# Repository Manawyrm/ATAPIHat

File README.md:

ATAPIHat
=============================

#### Overview

Replaced by https://github.com/Manawyrm/ATAPIHat-SMI  
Directly connected to the GPIOs, much higher speeds.   

**Don't manufacture this board (in either Rev.A or Rev.B).**  
This design isn't optimal at all. 

#### Rev. A Errata
Reset is wrong, is hardpulled to ground. Solution: connect to GPIO17.   
Chip select is non-ideal (solder jumper?)  
Selectable 5V/3.3V on Pin 20 required  
IDE Reset line should be connected to LED7 aka pin 28 of U4  
Signal integrity issues, paralell termination resistors (maybe 120 Ohms) and series termination would be ideal.  

#### Additional info

[Kernel driver](https://github.com/Manawyrm/pata-gpio)  
[Schematic](https://github.com/Manawyrm/ATAPIHat/blob/master/ATAPIHat.pdf)

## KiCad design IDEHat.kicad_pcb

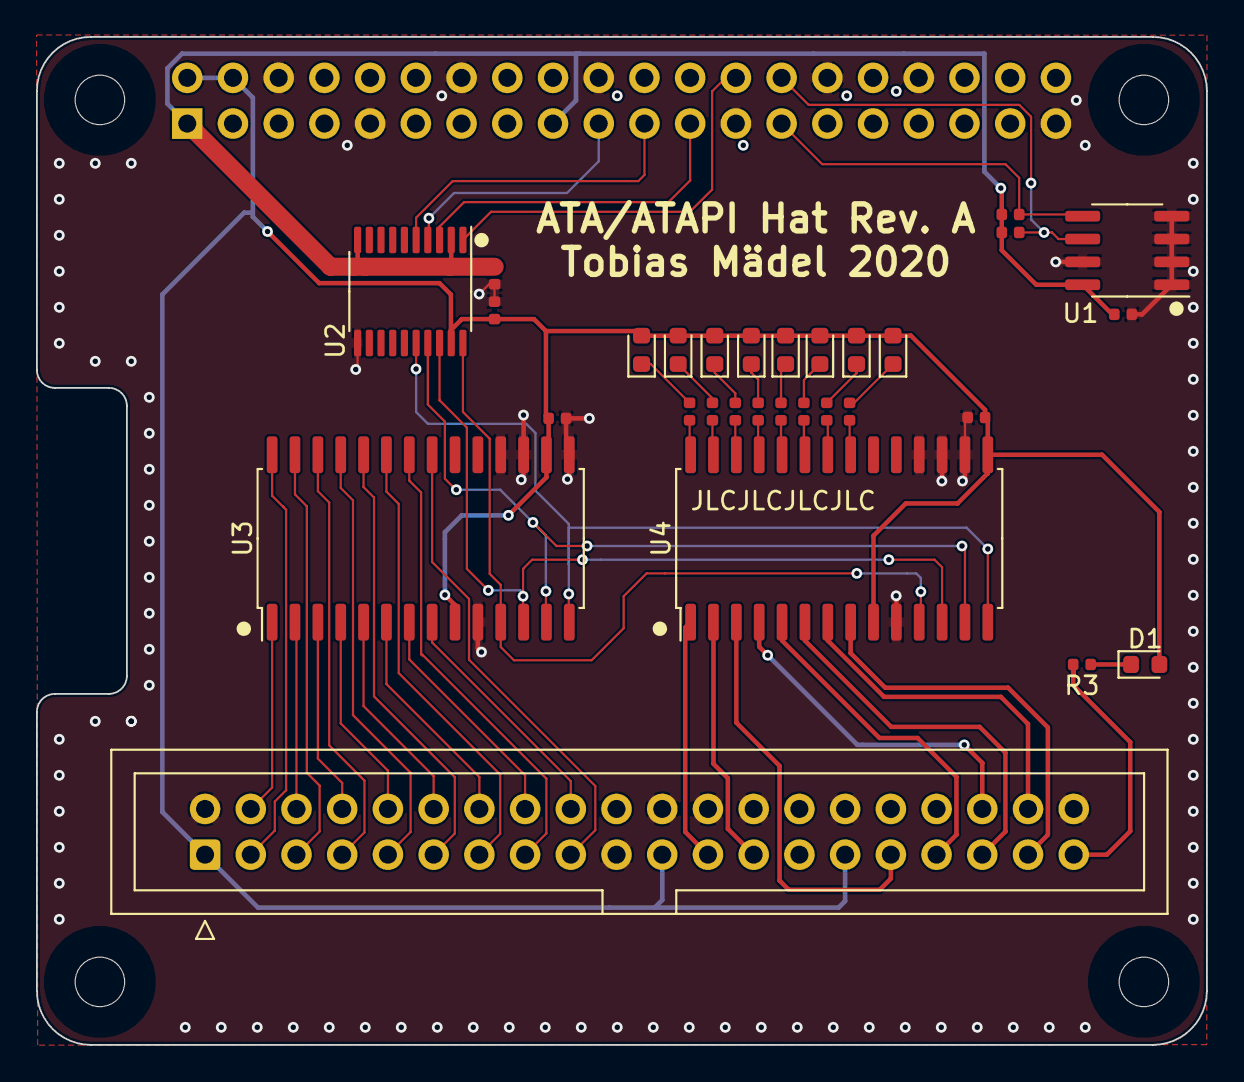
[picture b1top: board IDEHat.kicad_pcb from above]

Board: 2 copper layers, 65.0 x 56.0 mm, 31 parts (1 on the bottom side), 55 nets.

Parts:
C1, C2, C3, C4, C5: 100n; C_0402_1005Metric
D1: LED; LED_0603_1608Metric
D2, D3: Red; LED_0603_1608Metric
D4, D5: Yellow; LED_0603_1608Metric
D6, D7: Green; LED_0603_1608Metric
D8, D9: Blue; LED_0603_1608Metric
J1: Pi; PinSocket_2x20_P2.54mm_Vertical
J2: IDE; IDC-Header_2x20_P2.54mm_Vertical
R1, R2, R3, R4, R5, R6, R7, R10, R11: 4.7k; R_0402_1005Metric
R8, R9: 10k; R_0402_1005Metric
U1: AT24CS32; SOIC-8_3.9x4.9mm_P1.27mm
U2: TXS0108EPW; TSSOP-20_4.4x6.5mm_P0.65mm
U3, U4: MCP23S17_SO; SOIC-28W_7.5x17.9mm_P1.27mm

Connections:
+3V3: C4.1, C5.1, J1.1, J1.17, R1.1, R2.1, U1.8, U2.2, U2.10
+5V: C1.1, C2.1, C3.1, D1.2, D2.2, D3.2, D4.2, D5.2, D6.2, D7.2, D8.2, D9.2, J1.2, J1.4, J2.1, J2.21, J2.29, U2.19, U3.9, U3.16, U4.9, U4.15
/3V_CS: J1.26, U2.1
/3V_MISO: J1.21, U2.5
/3V_MOSI: J1.19, U2.4
/3V_SCK: J1.23, U2.3
/ACTIVE: J2.39, R3.2
/CS: U2.20, U3.11, U4.11
/CS0: J2.37, U4.8
/CS1: J2.38, U4.7
/D0: J2.17, U3.21
/D1: J2.15, U3.22
/D2: J2.13, U3.23
/D3: J2.11, U3.24
/D4: J2.9, U3.25
/D5: J2.7, U3.26
/D6: J2.5, U3.27
/D7: J2.3, U3.28
/D8: J2.4, U3.1
/D9: J2.6, U3.2
/D10: J2.8, U3.3
/D11: J2.10, U3.4
/D12: J2.12, U3.5
/D13: J2.14, U3.6
/D14: J2.16, U3.7
/D15: J2.18, U3.8
/DA0: J2.35, U4.6
/DA1: J2.33, U4.5
/DA2: J2.36, U4.4
/ID_SC: J1.28, R2.2, U1.6
/ID_SD: J1.27, R1.2, U1.5
/IOR: J2.25, U4.2
/IOW: J2.23, U4.1
/IRQ: J2.31, U4.3
/MISO: U2.16, U3.14, U4.14
/MOSI: U2.17, U3.13, U4.13
/SCK: U2.18, U3.12, U4.12
GND: C1.2, C2.2, C3.2, C4.2, C5.2, J1.6, J1.9, J1.14, J1.20, J1.25, J1.30, J1.34, J1.39, J2.2, J2.19, J2.22, J2.24, J2.26, J2.30, J2.40, U1.1, U1.2, U1.3, U1.4, U1.7, U2.11, U3.10, U3.15, U3.17, U3.18, U4.10, U4.16, U4.17, U4.18
unnamed: D1.1, R3.1
unnamed: D2.1, R4.1
unnamed: D3.1, R5.1
unnamed: D4.1, R6.1
unnamed: D5.1, R7.1
unnamed: D6.1, R8.1
unnamed: D7.1, R9.1
unnamed: D8.1, R10.1
unnamed: D9.1, R11.1
unnamed: R4.2, U4.21
unnamed: R5.2, U4.22
unnamed: R6.2, U4.23
unnamed: R7.2, U4.24
unnamed: R8.2, U4.25
unnamed: R9.2, U4.26
unnamed: R10.2, U4.27
unnamed: R11.2, U4.28

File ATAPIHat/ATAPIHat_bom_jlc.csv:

"Comment","Designator","Footprint","LCSC Part #"
"100n","C1,C2,C3,C4,C5","C_0402_1005Metric","C1525"
"LED","D1","LED_0603_1608Metric","C72043"
"Red","D2,D3","LED_0603_1608Metric","C2286"
"Yellow","D4,D5","LED_0603_1608Metric","C72038"
"Green","D6,D7","LED_0603_1608Metric","C72043"
"Blue","D8,D9","LED_0603_1608Metric","C72041"
"4.7k","R1,R2,R3,R4,R5,R6,R7,R10,R11","R_0402_1005Metric","C25900"
"10k","R8,R9","R_0402_1005Metric","C25744"
"AT24CS32","U1","SOIC-8_3.9x4.9mm_P1.27mm","C60583"
"TXS0108EPW","U2","TSSOP-20_4.4x6.5mm_P0.65mm","C17206"
"MCP23S17_SO","U3,U4","SOIC-28W_7.5x17.9mm_P1.27mm","C145413"

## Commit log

2020-07-13 Rename to ATAPIHat
2020-07-13 Create LICENSE
2020-08-02 ATAPIHat Rev A Errata
2020-08-02 Add readme entries
